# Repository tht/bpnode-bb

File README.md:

# *Blue Pill* Extender

There is a cheap, wildly available STTM3232F103C8T6 board out there. Because of it's shape and color it's called *Blue Pill* (BP). More details about this board can be found on [jeelabs](http://jeelabs.org/article/1649a/). There are *at least* two slightly different boards out there. This extension board is designed to match the BPs where the 2x03 pin header is next to `B11`, `B10` and `B1`. These are the boards where the USB connector is mounted in a cutout on the PCB. Other boards do have the USB connecter on top of the PCB and this 2x03 header is offset one pin – these boards will not fit nicely and need *creative* soldering as [shown here](https://cloud.githubusercontent.com/assets/148955/22704867/965d2520-ed69-11e6-9ae8-8ece3ff3e735.jpg).

The BP fits perfectly fine in a breadboard but it's missing the convenient programming headers for [SER+](http://jeelabs.org/article/1649f/) and some other features (see list below).

Thanks to the fantastic people over at jeelabs.org I was able to create this add-on board for the *Blue Pill* in KiCAD. This is how it will look like mounted on a BP.

## Features

* Programming header for programming the BP using a [SER+](http://jeelabs.org/article/1649f/) - including automatic reset of the target (BP)
* Area for mounting an RFM69-CW module
* Reset button
* Optimized for use on a breadboard

## Current State

Revision 1 is a little bit off-center but working perfectly fine.

There are some plans for the next revision of the board (see *Issues*). Some of them will probably become a completely different board as this one is meant to be used on a breadboard.

## Usage
The *Blue Pill Extender* (BPE) is mounted on top of an existing BP (label facing up). Make sure you solder the headers facing down to the BP first so it will fit into a breadboard before continuing here.

First prepare the BPE by soldering on the small resistors. The reset button is not required but may be helpful. Also add the RF module if you plan to use one. Make sure the RF module is not placed wrongly!

The 90° programming headers should be mounted from below (soldering on top) but they do work both ways.

Now remove the jumpers from the *BOOT?* pins on the BP and push the BPE on there. Make sure the 2x3 header of the *BOOT?* goes through the BPE and there there is still enough room to plug in an USB cable. Solder the 2x3 headers to the BPE. Now use some short wires (or leftover resistor legs) to connect all the outer BPE pins to the corresponding pins on the BP below – **DO NOT solder the antenna to the BP below!**

## References

* [Ser+ Programming Header](http://jeelabs.org/article/1649f/)
* [RFM69 CW Pinout](https://openenergymonitor.org/emon/sites/default/files/RFM69CW-V1.1_Hope_pinouts.jpg)
* [HyTiny Extender Layout](https://github.com/jeelabs/embello/blob/master/explore/1608-forth/tex/tex-v0.pdf)
* [BP Pinout](http://wiki.stm32duino.com/images/a/ae/Bluepillpinout.gif)

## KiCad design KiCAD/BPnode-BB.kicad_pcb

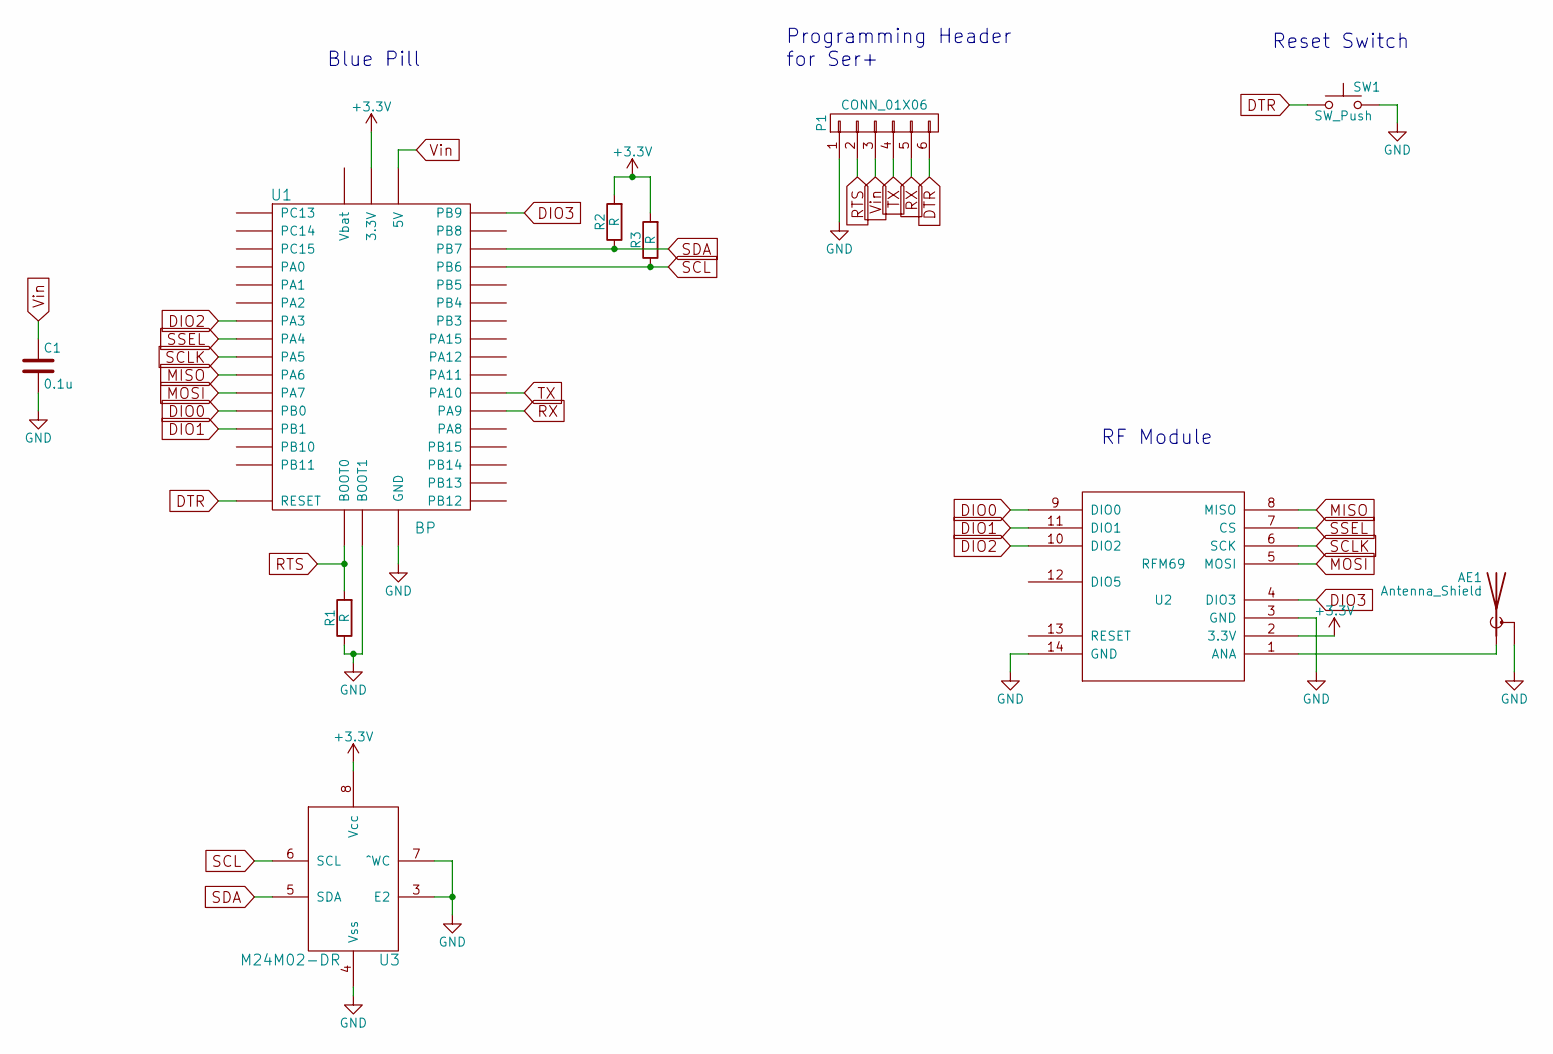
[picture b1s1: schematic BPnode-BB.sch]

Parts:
AE1: Antenna_Shield; U.FL-COAX
C1: 0.1u; C_0805_HandSoldering
P1: CONN_01X06; Pin_Header_Angled_1x06_Pitch2.54mm
R1, R2, R3: R; R_0805_HandSoldering
SW1: SW_Push; SMD_BUTTON
U1: BP; BLUEPILL-EXTENSION
U2: RFM69; RFM69CW
U3: M24M02-DR; SOIC-8_3.9x4.9mm_Pitch1.27mm

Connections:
+3V3: R2.2, R3.2, U1.3V3 (3.3V), U2.2 (3.3V), U3.8 (Vcc)
DIO0: U1.PB0, U2.9 (DIO0)
DIO1: U1.PB1, U2.11 (DIO1)
DIO2: U1.PA3, U2.10 (DIO2)
DIO3: U1.PB9, U2.4 (DIO3)
DTR: P1.6, SW1.1, U1.NRST (RESET)
GND: AE1.2 (Shield), C1.2, P1.1, R1.1, SW1.2, U1.G (GND), U1.PB2 (BOOT1), U2.3 (GND), U2.14 (GND), U3.3 (E2), U3.4 (Vss), U3.7 (^WC)
MISO: U1.PA6, U2.8 (MISO)
MOSI: U1.PA7, U2.5 (MOSI)
unnamed: AE1.1 (A), U2.1 (ANA)
RTS: P1.2, R1.2, U1.BOOT (BOOT0)
RX: P1.5, U1.PA9
SCL: R3.1, U1.PB6, U3.6 (SCL)
SCLK: U1.PA5, U2.6 (SCK)
SDA: R2.1, U1.PB7, U3.5 (SDA)
SSEL: U1.PA4, U2.7 (CS)
TX: P1.4, U1.PA10
Vin: C1.1, P1.3, U1.5V

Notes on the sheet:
RF Module
Reset Switch
Programming Header for Ser+
Blue Pill

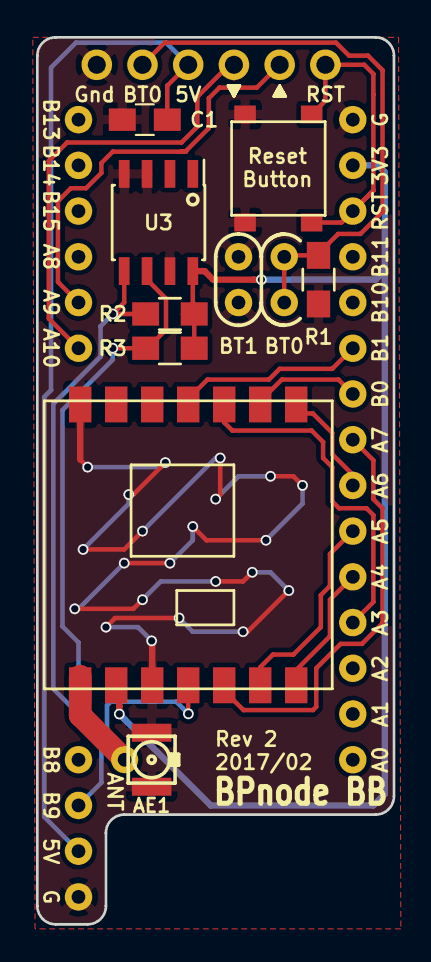
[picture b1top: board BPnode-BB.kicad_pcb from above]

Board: 2 copper layers, 19.8 x 49.3 mm, 10 parts (0 on the bottom side), 18 nets.

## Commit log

2017-01-09 Initial commit of board
2017-01-09 Ordered 2016_01_09
2017-01-11 Added schemata, fixes #4
2017-01-13 Initial version of readme
2017-01-30 Update after rev1 review
2017-01-30 Typos
2017-02-07 Documentation updated
2017-02-07 Added picture
2017-02-07 Added note about different boards
2017-02-07 Moved 2x03 header to get rid of the offset, #8
2017-02-11 Almost ready for rev2. fixes #9, fixes #8, fixes #1
2017-02-18 Removed unnecessary files
2017-02-18 On the way to rev2
2017-02-18 Renaming
2017-02-19 Ready for ordering
2017-02-26 Rev 2 as ordered
2017-02-26 added missing images
